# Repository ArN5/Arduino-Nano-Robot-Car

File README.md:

# Arduino-Nano-Robot-Car
This is for a class being taught at San Diego City Robotics, in which a low cost Arduino Nano base PCB that contains the L293D motor controller is used for basic robotics. The files will be open to the public along with the Arduino lessons and code. 

L293d_module.brd is the board file for a L293D module which was milled out on an othermill.
It just a simple module for 2 motors.

NanoBase_L293D.brd is a arduino nano module
which has a L293D module with screw terminals, made primarily to control some motors and be used as a simple robot platform.

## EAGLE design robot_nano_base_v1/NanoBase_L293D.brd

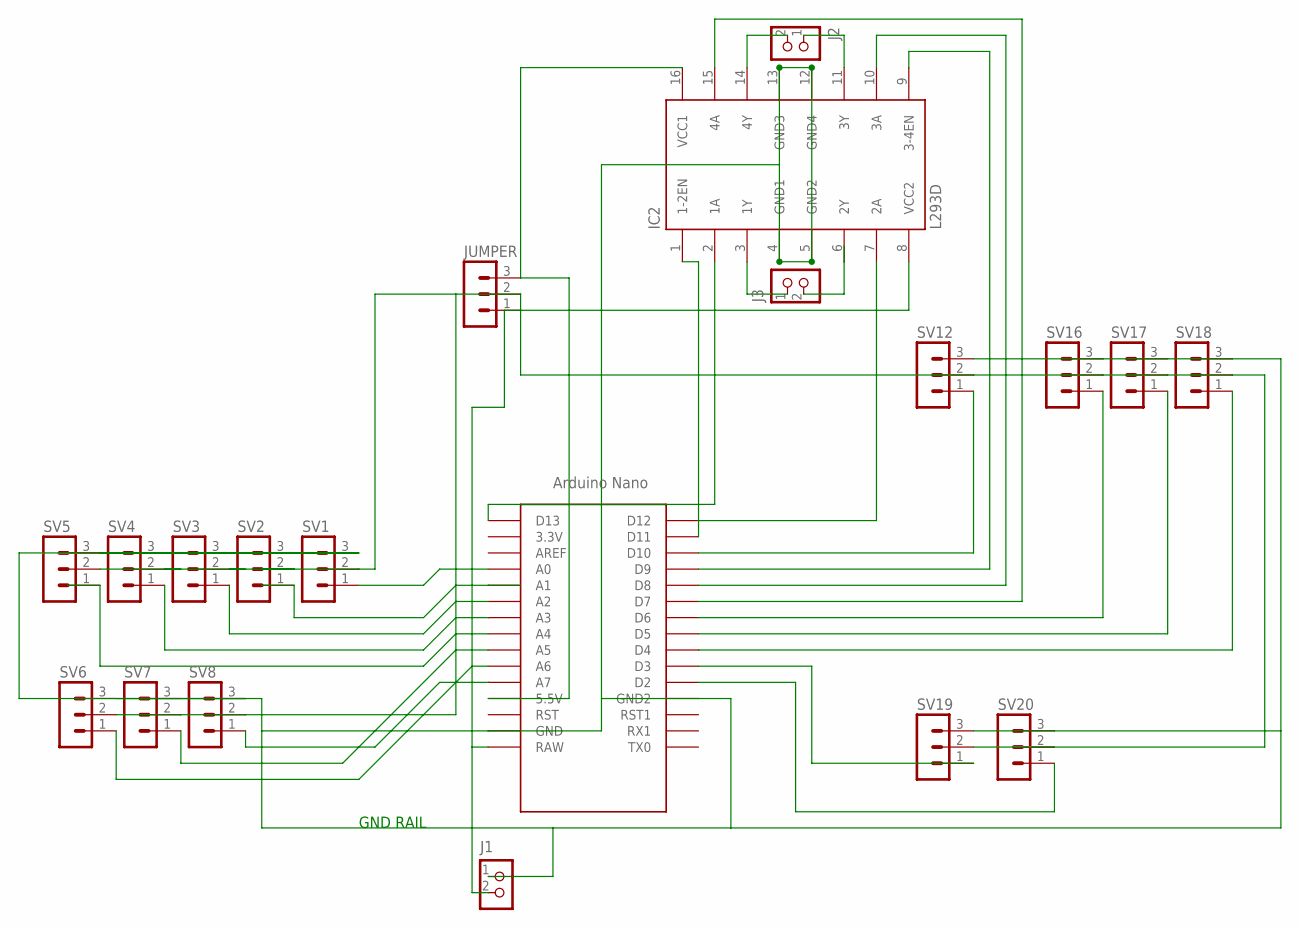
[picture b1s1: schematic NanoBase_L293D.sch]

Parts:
IC2: L293D; DIL16
J1, J2, J3: CON_TERMINAL_BLOCK_02-5MM; TERMINAL_BLOCK_2P_5
JUMPER: MA03-1
SV1, SV2, SV3, SV4, SV5, SV6, SV7, SV8, SV12, SV16, SV17, SV18, SV19, SV20: MA03-1
U$1: NANO

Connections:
5V: IC2.16 (VCC1), JUMPER.3, U$1.5V (5.5V)
A4: SV5.1, U$1.A4
A5: SV7.1, U$1.A5
D2: SV20.1, U$1.D2
D3: SV19.1, U$1.D3
D4: SV18.1, U$1.D4
D5: SV17.1, U$1.D5
D6: SV16.1, U$1.D6
D7-4A: IC2.15 (4A), U$1.D7
D8-3A: IC2.10 (3A), U$1.D8
D9-3-4EN: IC2.9 (3-4EN), U$1.D9
D10: SV12.1, U$1.D10
D11-1-2EN: IC2.1 (1-2EN), U$1.D11
D12-2A: IC2.7 (2A), U$1.D12
D13-1A: IC2.2 (1A), U$1.D13
GND: IC2.4 (GND1), IC2.5 (GND2), IC2.12 (GND4), IC2.13 (GND3), J1.1, SV1.3, SV2.3, SV3.3, SV4.3, SV5.3, SV6.3, SV7.3, SV8.3, SV12.3, SV16.3, SV17.3, SV18.3, SV19.3, SV20.3, U$1.GND, U$1.GND1 (GND2)
MIDDLERAIL: JUMPER.2, SV1.2, SV2.2, SV3.2, SV4.2, SV5.2, SV6.2, SV7.2, SV8.2
unnamed: SV1.1, U$1.A0
unnamed: SV3.1, U$1.A2
unnamed: SV4.1, U$1.A3
unnamed: SV12.2, SV16.2, SV17.2, SV18.2, SV19.2, SV20.2
unnamed: SV6.1, U$1.A6
unnamed: SV8.1, U$1.A7
unnamed: IC2.14 (4Y), J2.2
unnamed: IC2.11 (3Y), J2.1
unnamed: IC2.3 (1Y), J3.1
unnamed: IC2.6 (2Y), J3.2
unnamed: SV2.1, U$1.A1
VIN: IC2.8 (VCC2), J1.2, JUMPER.1, U$1.RAW

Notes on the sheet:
GND RAIL

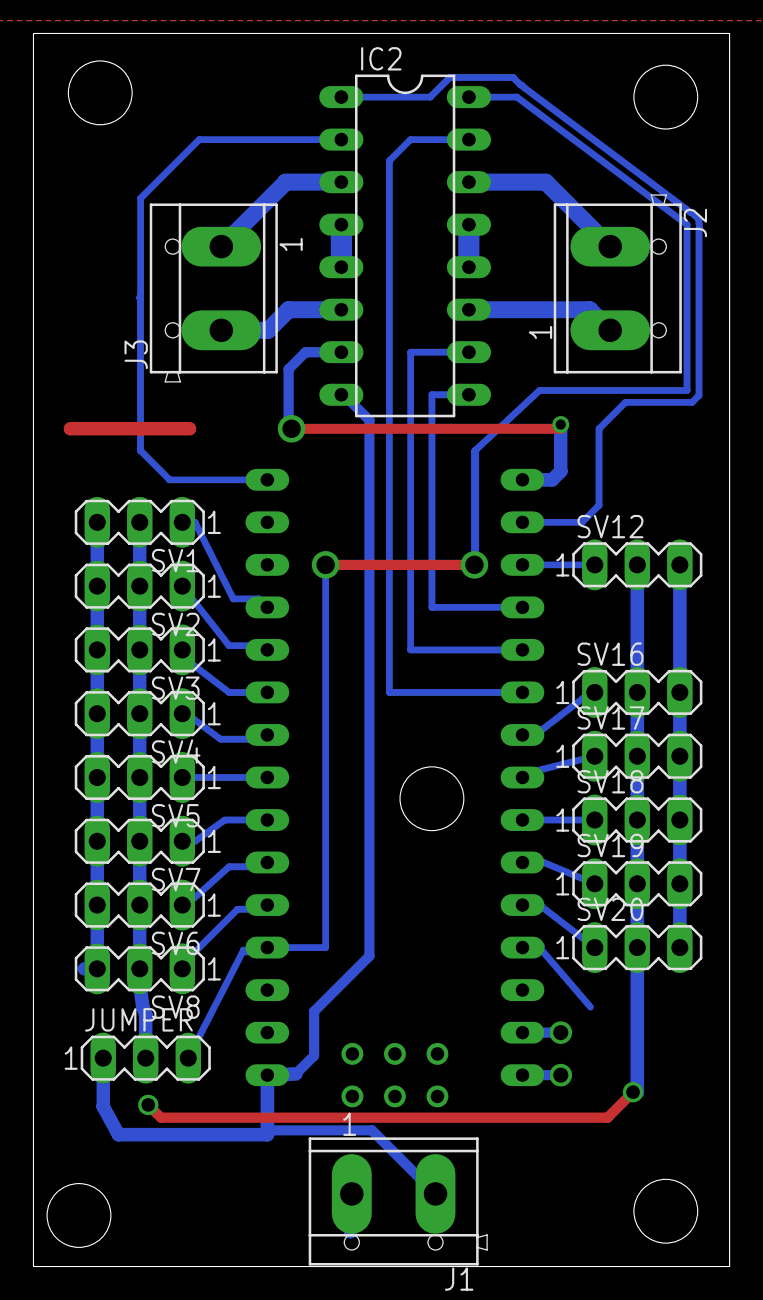
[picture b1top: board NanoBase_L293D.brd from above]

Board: 2 copper layers, 41.6 x 73.6 mm, 20 parts (0 on the bottom side), 29 nets.

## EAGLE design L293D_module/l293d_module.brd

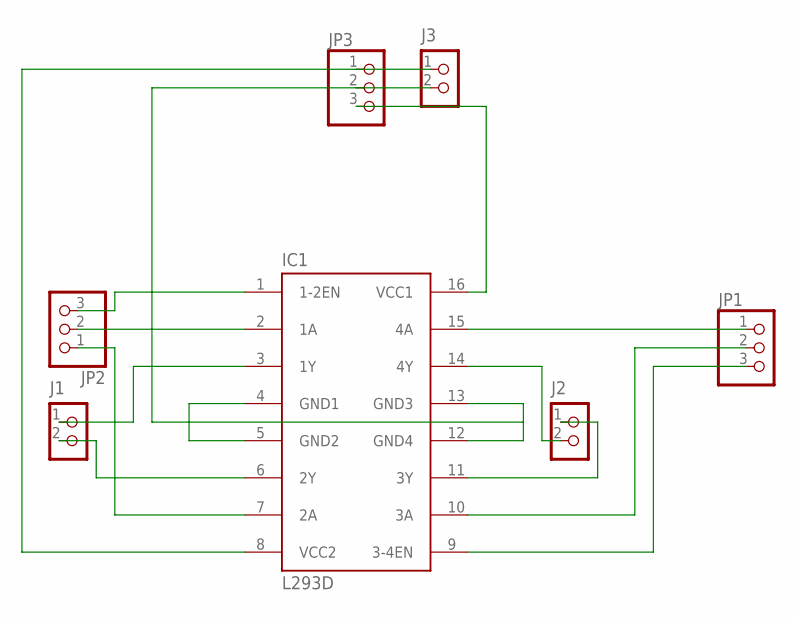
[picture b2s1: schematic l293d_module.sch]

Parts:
IC1: L293D; DIL16
J1, J2, J3: CON_TERMINAL_BLOCK_02-5MM; TERMINAL_BLOCK_2P_5
JP1, JP2, JP3: PINHD-1X3; 1X03

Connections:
1A: IC1.2 (1A), JP2.2
2A: IC1.7 (2A), JP2.1
3B: IC1.10 (3A), JP1.2
4B: IC1.15 (4A), JP1.1
5V: IC1.16 (VCC1), JP3.3
ENA: IC1.1 (1-2EN), JP2.3
ENB: IC1.9 (3-4EN), JP1.3
GND: IC1.4 (GND1), IC1.5 (GND2), IC1.12 (GND4), IC1.13 (GND3), J3.2, JP3.2
unnamed: IC1.3 (1Y), J1.1
unnamed: IC1.6 (2Y), J1.2
unnamed: IC1.14 (4Y), J2.2
unnamed: IC1.11 (3Y), J2.1
VIN: IC1.8 (VCC2), J3.1, JP3.1

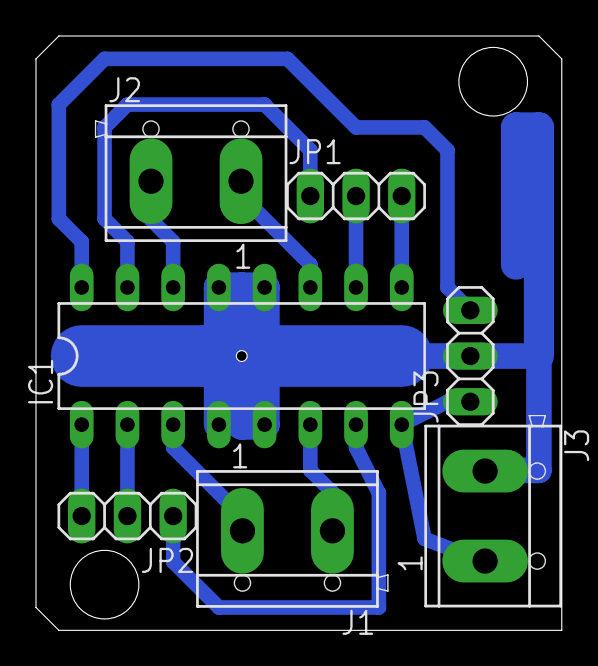
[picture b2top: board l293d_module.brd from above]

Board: 2 copper layers, 29.2 x 33.0 mm, 7 parts (0 on the bottom side), 13 nets.

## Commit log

2016-10-15 Add files via upload
    These are the Eagle files for the base and module for the L293D IC, the board only requires 2.54 pin headers and a Jumper (or female to female cable). These boards were designed specifically for the 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
2016-10-15 Create Code
2018-01-20 added more details to readme
    more details on the board files
2020-03-03 added the board I made in 2016 and some images
2020-03-03 removed some files
